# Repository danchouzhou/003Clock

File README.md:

# 003Clock

## Usage
### To clone this project
This project work with submodule from Nuvoton corporation. You need to initialize submodules by passing ``--recurse-submodules`` to the ``git clone`` command.
```
git clone https://github.com/danchouzhou/003Clock.git --recurse-submodules
```

### Build tools
Please make sure the installation path is the same as the one in `setting.json`.
- [SDCC 4.2.0](https://sourceforge.net/projects/sdcc/files/sdcc-win64/4.2.0/)
- [Nu-Link_Command_Tool_V3.17.7691r](https://www.nuvoton.com/tool-and-software/software-tool/programmer-tool/)

### Build the firmware
```
cd firmware/003Clock
```
Simply ``./build.bat``. ``main.bin`` should be inside the ``Objects`` folder.
```
./build.bat
```
### Flash the firmware by Nu-Link programmer (ICP)
```
./flash.bat
```
### Flash the firmware without a Nu-Link programmer (ISP)
1. Download the [NuMicro ISP Programming Tool](https://www.nuvoton.com/tool-and-software/software-tool/programmer-tool/)
2. Connect USB-UART adapter to PC
3. Select the COM port and then press `connect`\

4. Connect the target device to the USB-UART adapter, ISP Tool should show `connected`\

5. Select APROM file and check `APROM` and `Reset and Run`, then press `Start`\

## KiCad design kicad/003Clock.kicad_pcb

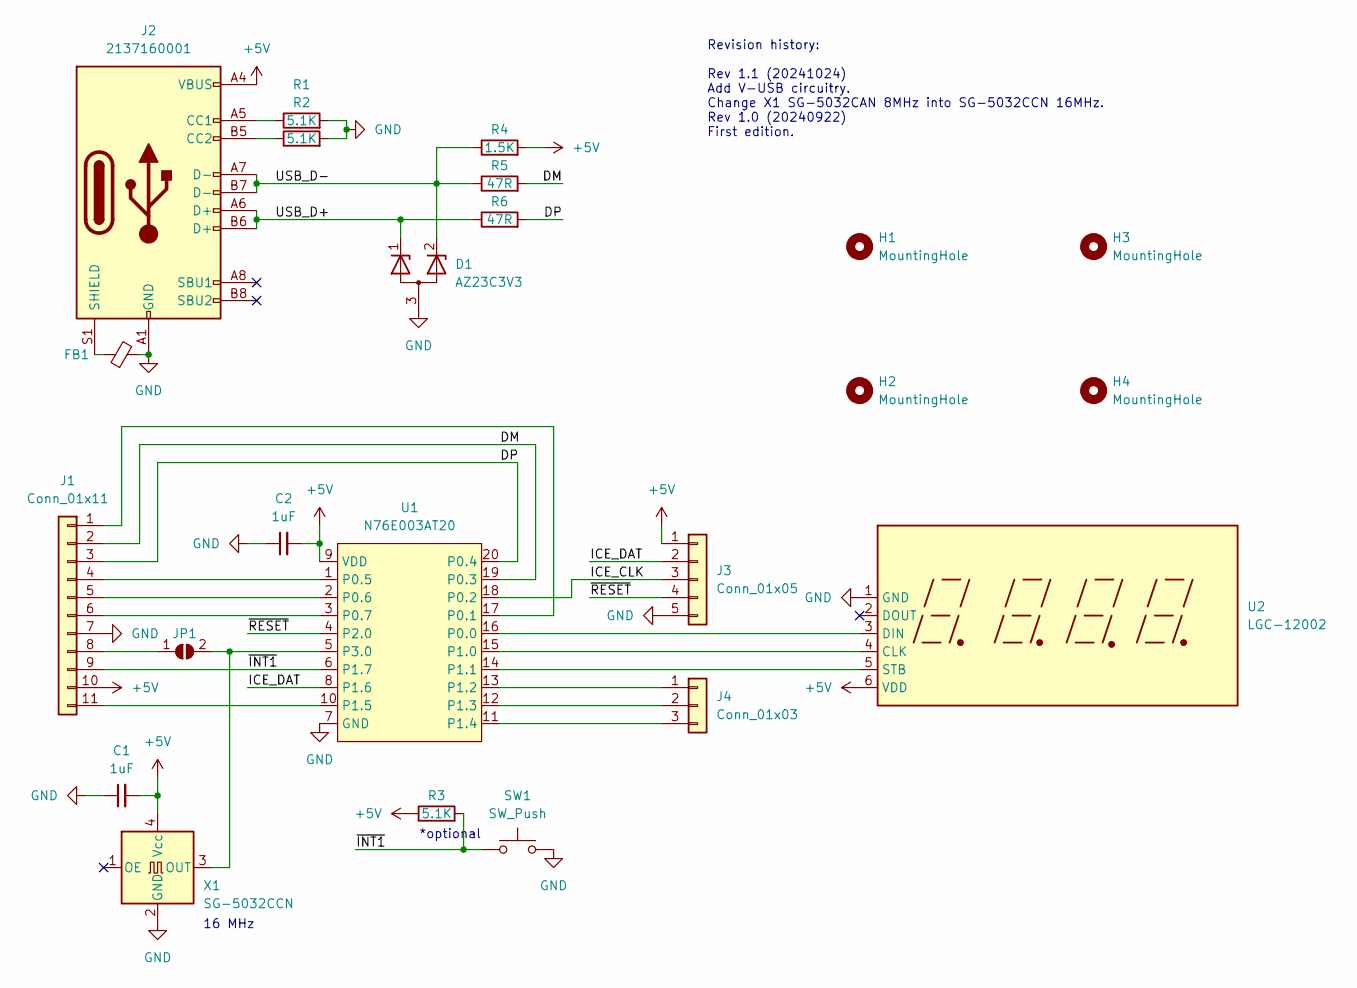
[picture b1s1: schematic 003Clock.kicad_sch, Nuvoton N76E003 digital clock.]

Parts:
C1, C2: 1uF; C_0805_2012Metric_Pad1.18x1.45mm_HandSolder
D1: AZ23C3V3; SOT-23-3
FB1: FerriteBead_Small; L_0805_2012Metric_Pad1.05x1.20mm_HandSolder
H1, H2, H3, H4: MountingHole; MountingHole_3.2mm_M3_ISO14580
J1: Conn_01x11; PinHeader_1x11_P2.54mm_Vertical
J2: 2137160001
J3: Conn_01x05; PinHeader_1x05_P2.54mm_Vertical
J4: Conn_01x03; PinHeader_1x03_P2.54mm_Vertical
JP1: SolderJumper_2_Open; SolderJumper-2_P1.3mm_Open_Pad1.0x1.5mm
R1, R2, R3: 5.1K; R_0805_2012Metric_Pad1.20x1.40mm_HandSolder
R4: 1.5K; R_0805_2012Metric_Pad1.20x1.40mm_HandSolder
R5, R6: 47R; R_0805_2012Metric_Pad1.20x1.40mm_HandSolder
SW1: SW_Push; SW_PUSH_6mm
U1: N76E003AT20; TSSOP-20_4.4x6.5mm_P0.65mm
U2: LGC-12002
X1: SG-5032CCN; Oscillator_SMD_SeikoEpson_SG8002LB-4Pin_5.0x3.2mm

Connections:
+5V: C1.2, C2.2, J1.10, J2.A4 (VBUS), J2.A9 (VBUS), J2.B4 (VBUS), J2.B9 (VBUS), J3.1, R3.1, R4.2, U1.9 (VDD), U2.6 (VDD), X1.4 (Vcc)
/DM: J1.2, R5.2, U1.19 (P0.3)
/DP: J1.3, R6.2, U1.20 (P0.4)
/ICE_CLK: J3.3, U1.18 (P0.2)
/ICE_DAT: J3.2, U1.8 (P1.6)
/USB_D+: D1.1 (K), J2.A6 (D+), J2.B6 (D+), R6.1
/USB_D-: D1.2 (K), J2.A7 (D-), J2.B7 (D-), R4.1, R5.1
/~INT1: J1.9, R3.2, SW1.1, U1.6 (P1.7)
/~RESET: J3.4, U1.4 (P2.0)
GND: C1.1, C2.1, D1.3 (A), FB1.2, J1.7, J2.A1 (GND), J2.A12 (GND), J2.B1 (GND), J2.B12 (GND), J3.5, R1.2, R2.2, SW1.2, U1.7 (GND), U2.1 (GND), X1.2 (GND)
unnamed: FB1.1, J2.S1 (SHIELD)
unnamed: J1.1, U1.17 (P0.1)
unnamed: J1.4, U1.1 (P0.5)
unnamed: J1.5, U1.2 (P0.6)
unnamed: J1.6, U1.3 (P0.7)
unnamed: J1.8, JP1.1 (A)
unnamed: J1.11, U1.10 (P1.5)
unnamed: J2.A5 (CC1), R1.1
unnamed: J2.B5 (CC2), R2.1
unnamed: J4.1, U1.13 (P1.2)
unnamed: J4.2, U1.12 (P1.3)
unnamed: J4.3, U1.11 (P1.4)
unnamed: JP1.2 (B), U1.5 (P3.0), X1.3 (OUT)
unnamed: U1.14 (P1.1), U2.5 (STB)
unnamed: U1.15 (P1.0), U2.4 (CLK)
unnamed: U1.16 (P0.0), U2.3 (DIN)

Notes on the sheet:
16 MHz
*optional
Revision history: Rev 1.1 (20241024) Add V-USB circuitry. Change X1 SG-5032CAN 8MHz into SG-5032CCN 16MHz. Rev 1.0 (20240922) First edition.

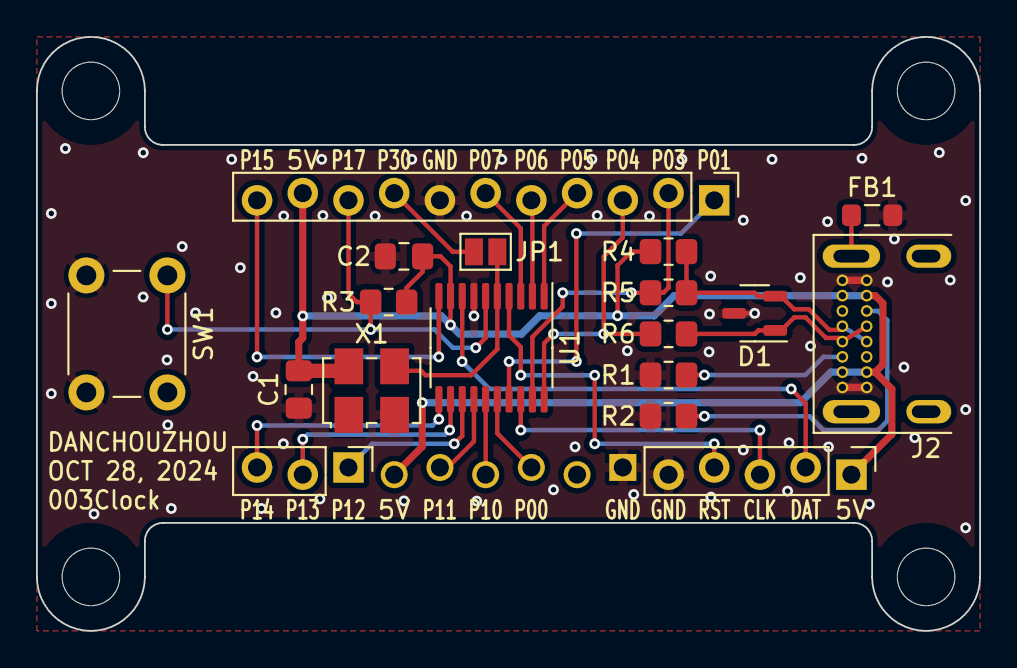
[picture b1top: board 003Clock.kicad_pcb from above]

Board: 2 copper layers, 52.4 x 33.0 mm, 23 parts (1 on the bottom side), 26 nets.

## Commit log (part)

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2025-02-10 Add Tachometer
2025-02-24 1. Fix P/N not recognize in ISP Tool
    2. Update README.md

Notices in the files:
kicad/003Clock.kicad_sch:
Copyright © Danny Chou, all rights reserved.
